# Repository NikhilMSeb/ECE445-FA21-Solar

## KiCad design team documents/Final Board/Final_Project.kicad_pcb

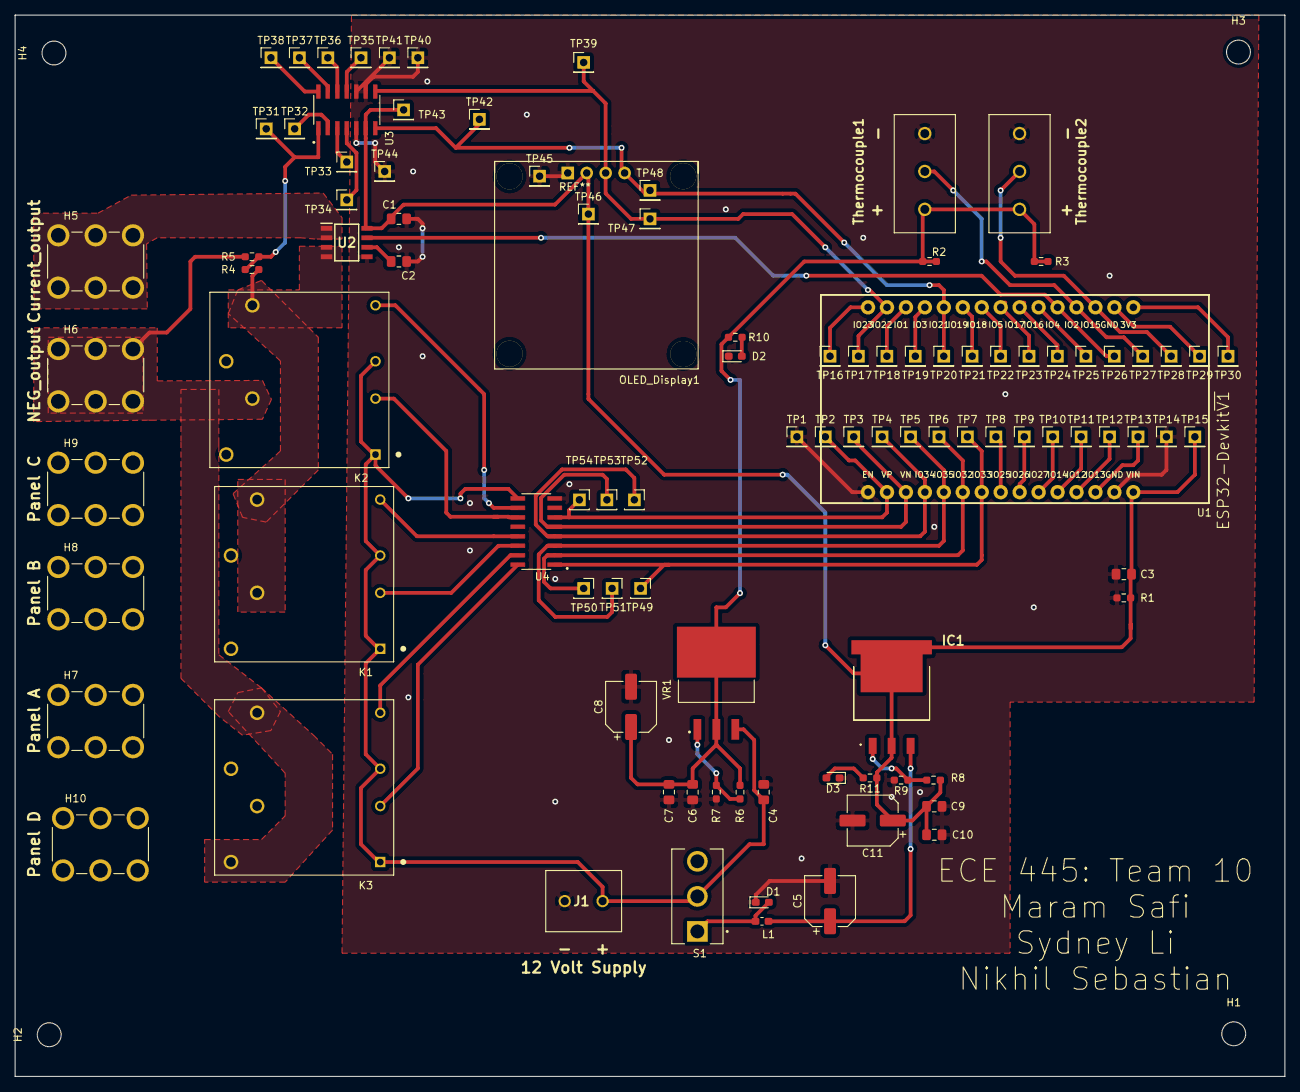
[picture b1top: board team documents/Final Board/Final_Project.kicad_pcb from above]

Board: 2 copper layers, 170.2 x 142.2 mm, 104 parts (0 on the bottom side), 59 nets.

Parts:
C1, C3, C6, C9: 0.1u; C_0805_2012Metric_Pad1.18x1.45mm_HandSolder
C2: 1n; C_0805_2012Metric_Pad1.18x1.45mm_HandSolder
C4, C7, C10: 10u; C_0805_2012Metric_Pad1.18x1.45mm_HandSolder
C5, C8, C11: 47u; CP_Elec_6.3x5.8
D1: D; D_0603_1608Metric_Pad1.05x0.95mm_HandSolder
D2, D3: LED; D_0603_1608Metric_Pad1.05x0.95mm_HandSolder
H1, H2, H3, H4: MountingHole; MountingHole_3.2mm_M3
H5: POS_output; KEYSTONE_8197
H6: NEG_output; KEYSTONE_8197
H7: Panel A; KEYSTONE_8197
H8: Panel B; KEYSTONE_8197
H9: Panel C; KEYSTONE_8197
H10: Panel D; KEYSTONE_8197
IC1: LM1117SX-5.0_NOPB; LM1117SX50NOPB
J1: Screw_Terminal_01x02; 2828372
K1, K2, K3: FTR-J2AK006W; RELAY_FTR-J2AK006W
L1: 100u; L_0603_1608Metric_Pad1.05x0.95mm_HandSolder
OLED_Display1: Conn_01x04; OLEDdisplay
R1: 10k; R_0603_1608Metric_Pad0.98x0.95mm_HandSolder
R2, R3: 4.7k; R_0603_1608Metric_Pad0.98x0.95mm_HandSolder
R4: 82K; R_0603_1608Metric_Pad0.98x0.95mm_HandSolder
R5: 3K; R_0603_1608Metric_Pad0.98x0.95mm_HandSolder
R6, R8: 240; R_0603_1608Metric_Pad0.98x0.95mm_HandSolder
R7: 390; R_0603_1608Metric_Pad0.98x0.95mm_HandSolder
R9: 715; R_0603_1608Metric_Pad0.98x0.95mm_HandSolder
R10, R11: 1k; R_0603_1608Metric_Pad0.98x0.95mm_HandSolder
S1: 100SP1T1B4M2QE; SW_100SP1T1B4M2QE
TP1, TP2, TP3, TP4, TP5, TP6, TP7, TP8, TP9, TP10, TP11, TP12, TP13, TP14, TP15, TP16, TP17, TP18, TP19, TP20, TP21, TP22, TP23, TP24, TP25, TP26, TP27, TP28, TP29, TP30, TP31, TP32, TP33, TP34, TP35, TP36, TP37, TP38, TP39, TP40, TP41, TP42, TP43, TP44, TP45, TP46, TP47, TP48: TestPoint; PinHeader_1x01_P2.54mm_Vertical
TP49, TP50, TP51, TP52, TP53, TP54: TestPoint; PinSocket_1x01_P2.54mm_Vertical
Thermocouple1, Thermocouple2: Screw_Terminal_01x03; 2828373
U1: ESP32DEVKITV1; ESP32-DEVKITV1
U2: ACS714xLCTR-30A; SOIC127P600X175-8N
U3: MCP3428-E_SL; SOIC127P600X175-14N
U4: ULN2003BDR; SOIC127P600X175-16N
VR1: LM1117SX-3.3_NOPB; TO254P1435X464-4N

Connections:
+3V3: C6.1, C7.1, C8.1, R2.1, R2.2, R3.1, R3.2, R6.1, R10.1, Thermocouple1.1, Thermocouple2.1, VR1.2, VR1.4
+5V: C1.2, C3.1, C9.1, C10.1, C11.1, IC1.2, IC1.4, IC1.5, OLED_Display1.2, R1.1, R8.1, R11.1, TP15.1, TP43.1, TP46.1, U1.30, U2.8, U3.6
+12V: C4.1, J1.2, K1.1, K1.3, K2.1, K2.3, K3.1, K3.3, S1.2, U4.9, VR1.3
Control_Signal1: TP2.1, TP54.1, U1.17, U4.6
Control_Signal2: TP3.1, TP53.1, U1.18, U4.5
Control_Signal3: TP4.1, TP52.1, U1.19, U4.4
Control_Signal4: TP5.1, TP51.1, U1.20, U4.3
Control_Signal5: TP6.1, TP50.1, U1.21, U4.2
Control_Signal6: TP7.1, TP49.1, U1.22, U4.1
Current_output: H5.1, H5.2, H5.3, H5.4, H5.5, H5.6, U2.1, U2.2
Current_output_voltage: TP26.1, U1.5, U2.7
GND: TP32.1, U3.2
GND1: C1.1, C2.1, C3.2, C4.2, C5.2, C6.2, C7.2, C8.2, C9.2, C10.2, C11.2, D1.1, D2.1, D3.1, J1.1, OLED_Display1.1, R1.2, R7.2, R9.2, TP1.1, TP14.1, TP40.1, TP41.1, TP44.1, TP45.1, Thermocouple1.3, Thermocouple2.3, U1.16, U1.29, U2.5, U3.5, U3.9, U3.10, U4.8
NEG_output: H6.1, H6.2, H6.3, H6.4, H6.5, H6.6, K2.6, K3.5, K3.8, R5.2
unnamed: C2.2, U2.6
unnamed: C5.1, IC1.3, L1.1
unnamed: D1.2, L1.2, S1.1
unnamed: D2.2, R10.2
unnamed: D3.2, R11.2
unnamed: IC1.1, R8.2, R9.1
unnamed: K1.2, U4.14
unnamed: K1.4, U4.13
unnamed: K2.2, U4.11
unnamed: K2.4, U4.10
unnamed: K3.2, U4.16
unnamed: K3.4, U4.15
unnamed: R6.2, R7.1, VR1.1
unnamed: TP8.1, U1.23
unnamed: TP9.1, U1.24
unnamed: TP10.1, U1.25
unnamed: TP11.1, U1.26
unnamed: TP12.1, U1.27
unnamed: TP13.1, U1.28
unnamed: TP16.1, U1.15
unnamed: TP18.1, U1.13
unnamed: TP19.1, U1.12
unnamed: TP21.1, U1.10
unnamed: TP22.1, U1.9
unnamed: TP23.1, U1.8
unnamed: TP24.1, U1.7
unnamed: TP25.1, U1.6
unnamed: TP29.1, U1.2
unnamed: TP30.1, U1.1
unnamed: TP33.1, U3.3
unnamed: TP34.1, U3.4
unnamed: TP35.1, U3.11
unnamed: TP36.1, U3.12
unnamed: TP37.1, U3.13
unnamed: TP38.1, U3.14
POS_output: K1.6, K1.8, K2.8, R4.1, U2.3, U2.4
Panel_A: H7.1, H7.2, H7.3, H7.4, H7.5, H7.6, K1.5
Panel_B: H8.1, H8.2, H8.3, H8.4, H8.5, H8.6, K1.7
Panel_C: H9.1, H9.2, H9.3, H9.4, H9.5, H9.6, K2.5, K2.7
Panel_D: H10.1, H10.2, H10.3, H10.4, H10.5, H10.6, K3.6, K3.7
SCL: OLED_Display1.3, TP17.1, TP39.1, TP47.1, U1.14, U3.8
SDA: OLED_Display1.4, TP20.1, TP42.1, TP48.1, U1.11, U3.7
Temp_Output: TP27.1, Thermocouple1.2, U1.4
Temp_Output1: TP28.1, Thermocouple2.2, U1.3
VOLT_output: R4.2, R5.1, TP31.1, U3.1

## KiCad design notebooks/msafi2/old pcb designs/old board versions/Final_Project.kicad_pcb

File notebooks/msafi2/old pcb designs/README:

Old PCB design files on Kicad
Final Board design can be found in Board folder in main fork.

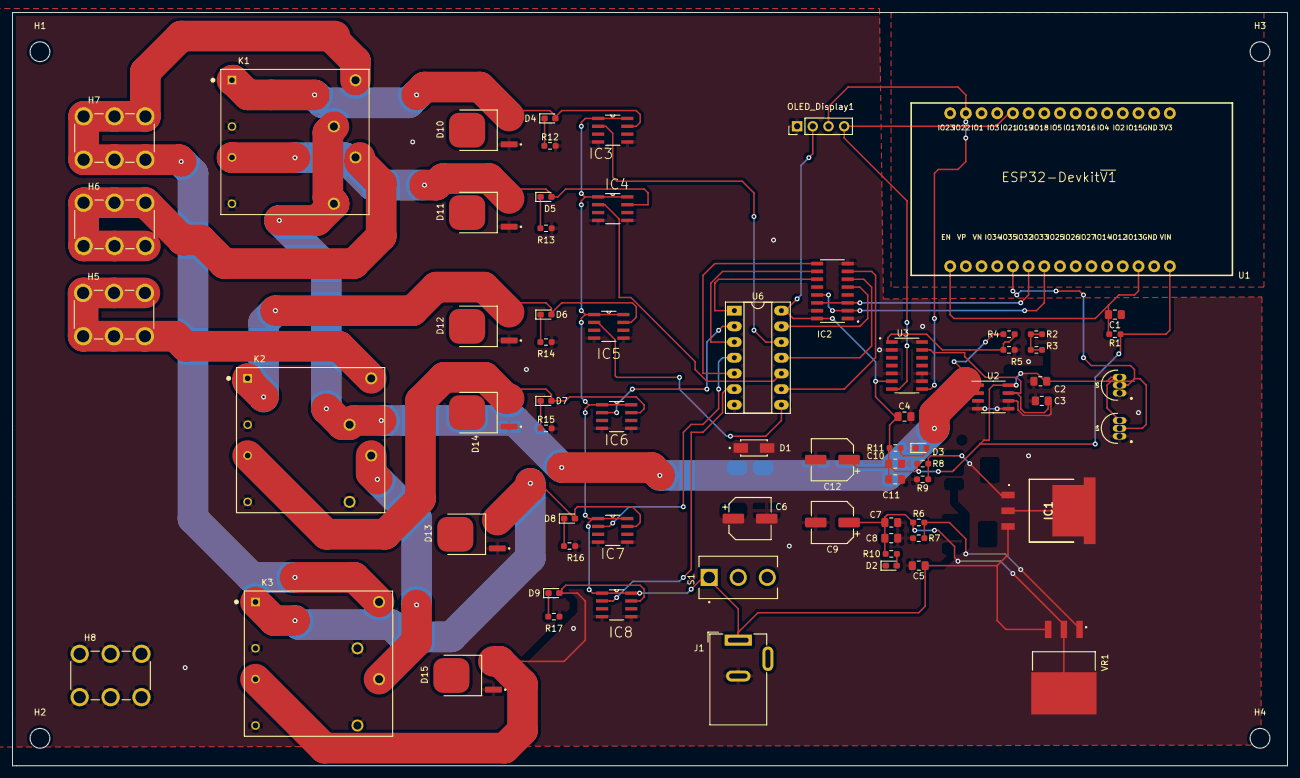
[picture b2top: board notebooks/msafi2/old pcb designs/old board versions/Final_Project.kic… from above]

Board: 2 copper layers, 206.4 x 121.9 mm, 73 parts (0 on the bottom side), 46 nets.

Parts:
C1, C2, C4, C7, C10: 0.1u; C_0805_2012Metric_Pad1.18x1.45mm_HandSolder
C3: 1n; C_0805_2012Metric_Pad1.18x1.45mm_HandSolder
C5, C8, C11: 10u; C_0805_2012Metric_Pad1.18x1.45mm_HandSolder
C6, C9, C12: 47u; CP_Elec_6.3x5.8
D1: D_Schottky; DIOM5226X240N
D2, D3, D4, D5, D6, D7, D8, D9: LED; D_0603_1608Metric_Pad1.05x0.95mm_HandSolder
D10, D11, D12, D13, D14, D15: DIODE; DPAK228P987X240-3N
H1, H2, H3, H4: MountingHole; MountingHole_3.2mm_M3
H5: Panel A; KEYSTONE_8197
H6: Panel B; KEYSTONE_8197
H7: Panel C; KEYSTONE_8197
H8: Panel D; KEYSTONE_8197
IC1: LM1117SX-5.0_NOPB; LM1117SX50NOPB
IC2: SN74HC139D; SOIC127P600X175-16N
IC3, IC4, IC5, IC6, IC7, IC8: MCP1407T-E_SN; SOIC127P600X175-8N
J1: Barrel_Jack_MountingPin; BarrelJack_Wuerth_6941xx301002
K1, K2, K3: FTR-J2AK006W; RELAY_FTR-J2AK006W
OLED_Display1: Conn_01x04; PinHeader_1x04_P2.54mm_Vertical
R1: 10k; R_0603_1608Metric_Pad0.98x0.95mm_HandSolder
R2, R3: 4.7k; R_0603_1608Metric_Pad0.98x0.95mm_HandSolder
R4: 82K; R_0603_1608Metric_Pad0.98x0.95mm_HandSolder
R5: 3K; R_0603_1608Metric_Pad0.98x0.95mm_HandSolder
R6, R8: 240; R_0603_1608Metric_Pad0.98x0.95mm_HandSolder
R7: 390; R_0603_1608Metric_Pad0.98x0.95mm_HandSolder
R9: 715; R_0603_1608Metric_Pad0.98x0.95mm_HandSolder
R10, R11: 1k; R_0603_1608Metric_Pad0.98x0.95mm_HandSolder
R12, R13, R14, R15, R16, R17: 560; R_0603_1608Metric_Pad0.98x0.95mm_HandSolder
S1: 100SP1T1B4M2QE; SW_100SP1T1B4M2QE
U1: ESP32DEVKITV1; ESP32-DEVKITV1
U2: ACS714xLCTR-30A; SOIC-8_3.9x4.9mm_P1.27mm
U3: MCP3428-E_SL; SOIC127P600X175-14N
U4, U5: DS18B20; TO-92-TO92127P495H2044-3
U6: SN74HCT04PW; DIP-14_W7.62mm_Socket_LongPads
VR1: LM1117SX-3.3_NOPB; TO254P1435X464-4N

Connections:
+3V3: C7.1, C8.1, C9.1, R2.1, R2.2, R3.1, R3.2, R6.1, R10.1, U4.3, U5.3, VR1.2, VR1.4
+5V: C2.2, C4.1, C10.1, C11.1, C12.1, IC1.2, IC1.4, IC1.5, IC2.16, OLED_Display1.2, R1.1, R8.1, R11.1, U1.30, U2.8, U3.6, U6.14
+12V: C5.1, C6.1, IC1.3, IC3.1, IC3.8, IC4.1, IC4.8, IC5.1, IC5.8, IC6.1, IC6.8, IC7.1, IC7.8, IC8.1, IC8.8, J1.1, S1.1, VR1.3
Control_Signal: IC2.2, IC2.13, U1.22
Control_Signal1: IC2.3, IC2.14, U1.21
Current_output_voltage: U2.7, U3.13
NEG_output: C2.1, C3.1, C4.2, C5.2, C6.2, C7.2, C8.2, C9.2, C10.2, C11.2, C12.2, D2.1, D3.1, D10.1, D11.1, D12.1, D13.1, D14.1, D15.1, H8.1, H8.2, H8.3, H8.4, H8.5, H8.6, IC2.1, IC2.8, IC2.15, IC3.4, IC3.5, IC4.4, IC4.5, IC5.4, IC5.5, IC6.4, IC6.5, IC7.4, IC7.5, IC8.4, IC8.5, J1.2, K1.2, K1.4, K2.2, K2.4, K2.8, K3.2, K3.4, K3.6, K3.8, OLED_Display1.1, R5.2, R7.2, R9.2, R12.2, R13.2, R14.2, R15.2, R16.2, R17.2, U2.3, U2.4, U2.5, U3.2, U3.5, U3.9, U3.10, U3.14, U4.1, U5.1, U6.7
unnamed: C3.2, U2.6
unnamed: D2.2, R10.2
unnamed: D3.2, R11.2
unnamed: D4.1, R12.1
unnamed: D5.1, R13.1
unnamed: D6.1, R14.1
unnamed: D7.1, R15.1
unnamed: D8.1, R16.1
unnamed: D9.1, R17.1
unnamed: D4.2, D10.2, IC3.7, K1.1
unnamed: D5.2, D11.2, IC4.7, K1.3
unnamed: D6.2, D12.2, IC5.7, K2.1
unnamed: D8.2, D13.2, IC7.7, K3.1
unnamed: D7.2, D14.2, IC6.7, K2.3
unnamed: D9.2, D15.2, IC8.7, K3.3
unnamed: IC1.1, R8.2, R9.1
unnamed: IC2.5, U6.13
unnamed: IC2.6, U6.11
unnamed: IC2.7, U6.9
unnamed: IC2.9, U6.5
unnamed: IC2.10, U6.3
unnamed: IC2.11, U6.1
unnamed: IC3.2, U6.12
unnamed: IC4.2, U6.10
unnamed: IC5.2, U6.8
unnamed: IC6.2, U6.2
unnamed: IC7.2, U6.4
unnamed: IC8.2, U6.6
unnamed: R6.2, R7.1, VR1.1
POS_output: K1.6, K1.8, K2.6, R4.1, U2.1, U2.2
Panel_A: H5.1, H5.2, H5.3, H5.4, H5.5, H5.6, K2.5
Panel_B: H6.1, H6.2, H6.3, H6.4, H6.5, H6.6, K1.7
Panel_C: H7.1, H7.2, H7.3, H7.4, H7.5, H7.6, K1.5, K3.5
Panel_D: K2.7, K3.7
RESET: C1.2, R1.2, U1.16, U1.28
SCL: OLED_Display1.3, U1.14, U3.8
SDA: OLED_Display1.4, U1.11, U3.7
Temp_Output: U1.20, U4.2, U5.2
VOLT_output: R4.2, R5.1, U3.1

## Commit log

2021-09-14 Update Design Structure
2021-10-29 Create New Changes
2021-11-01 Updating working parts of Django framework
2021-11-02 Adding Individual Progress Report to Notebook entries
2021-11-06 Add files via upload
    Darlington Array Configuration
2021-11-09 Updating Notebook Entries till 11/08/2021 (Part 1)
2021-11-09 Updating Notebook entries till 11/08/2021 (Part 2)
2021-11-09 Small typo
2021-11-09 Updating src folder with documentation and Arduino folder
2021-11-09 Updating Django project README
2021-11-09 Updating Arduino Code README
2021-11-10 Create PCB_files
2021-11-10 Create test
2021-11-13 Updating ESP32 POST files (basic)
2021-11-13 Adding notes to Notebook Entries for updating (ESP32)
2021-11-14 Microcontroller Research and Design Proposal
2021-11-14 Reformatting ESP32 Microcontroller Section
2021-11-14 Design Document First Draft
2021-11-14 Rooftop Visit w/ Kevin
2021-11-14 Added Attabox Image
2021-11-14 Relay Board Name Update
2021-11-15 Final Design Document
2021-11-15 PCB Updates
2021-11-16 Voltage Monitoring
2021-11-16 I2C Communication with ESP32
2021-11-16 Adding notes for later update (Django+Microcontroller)
2021-11-16 Update test
2021-11-16 Rename test to README
2021-11-16 Update and rename test to README
2021-11-18 Power Subsystem LTSpice Simulations
2021-11-19 Relay Subsystem Operation
2021-11-19 Finalized Relay Subsystem
2021-11-19 Typo in Relay Subsystem Fix
2021-11-19 Added Entry Link for Finalized Relay Subsystem
2021-11-19 Small Typo in Entry
2021-11-19 Small Typo In Latest Entry
2021-11-20 Code for Power Subsystem Calculations
2021-11-20 Monitoring Subsystem
2021-11-20 Adding an entry for the monitoring subsystem
2021-11-28 PCB Retrieval and Additional Testing
2021-11-30 ADC Testing and New Problems
2021-11-30 Rearranging Team Docs
2021-11-30 Updating Arduino programming so far
2021-11-30 Removing outdated Design Document
2021-11-30 Current Sensor
2021-11-30 Adding notes for completing all notebook entries
2021-12-02 Updating notebook (completing later)
2021-12-03 Fixes and Current Sensor Calibration
2021-12-03 Culmination of the Monitoring Subsystem
2021-12-04 Updating notebook for later completion
2021-12-04 Updating all Source code for the project
2021-12-04 Re-adding README for Django code
2021-12-04 Final Demo Presentation
2021-12-06 Final notes into notebook, Need to update properly
2021-12-06 Updated Entry
2021-12-07 Block Diagram Update
2021-12-10 Completing Notebook, Part 1
2021-12-10 Updating Final Team Documents; Updating Final Demo Code
2021-12-10 Arduino Code README typo
2021-12-10 Updating Django Code README
2021-12-10 Updating Notebook, Part 2
2021-12-10 Updating Notebook, Part 3
2021-12-10 Completed updating Notebook!
